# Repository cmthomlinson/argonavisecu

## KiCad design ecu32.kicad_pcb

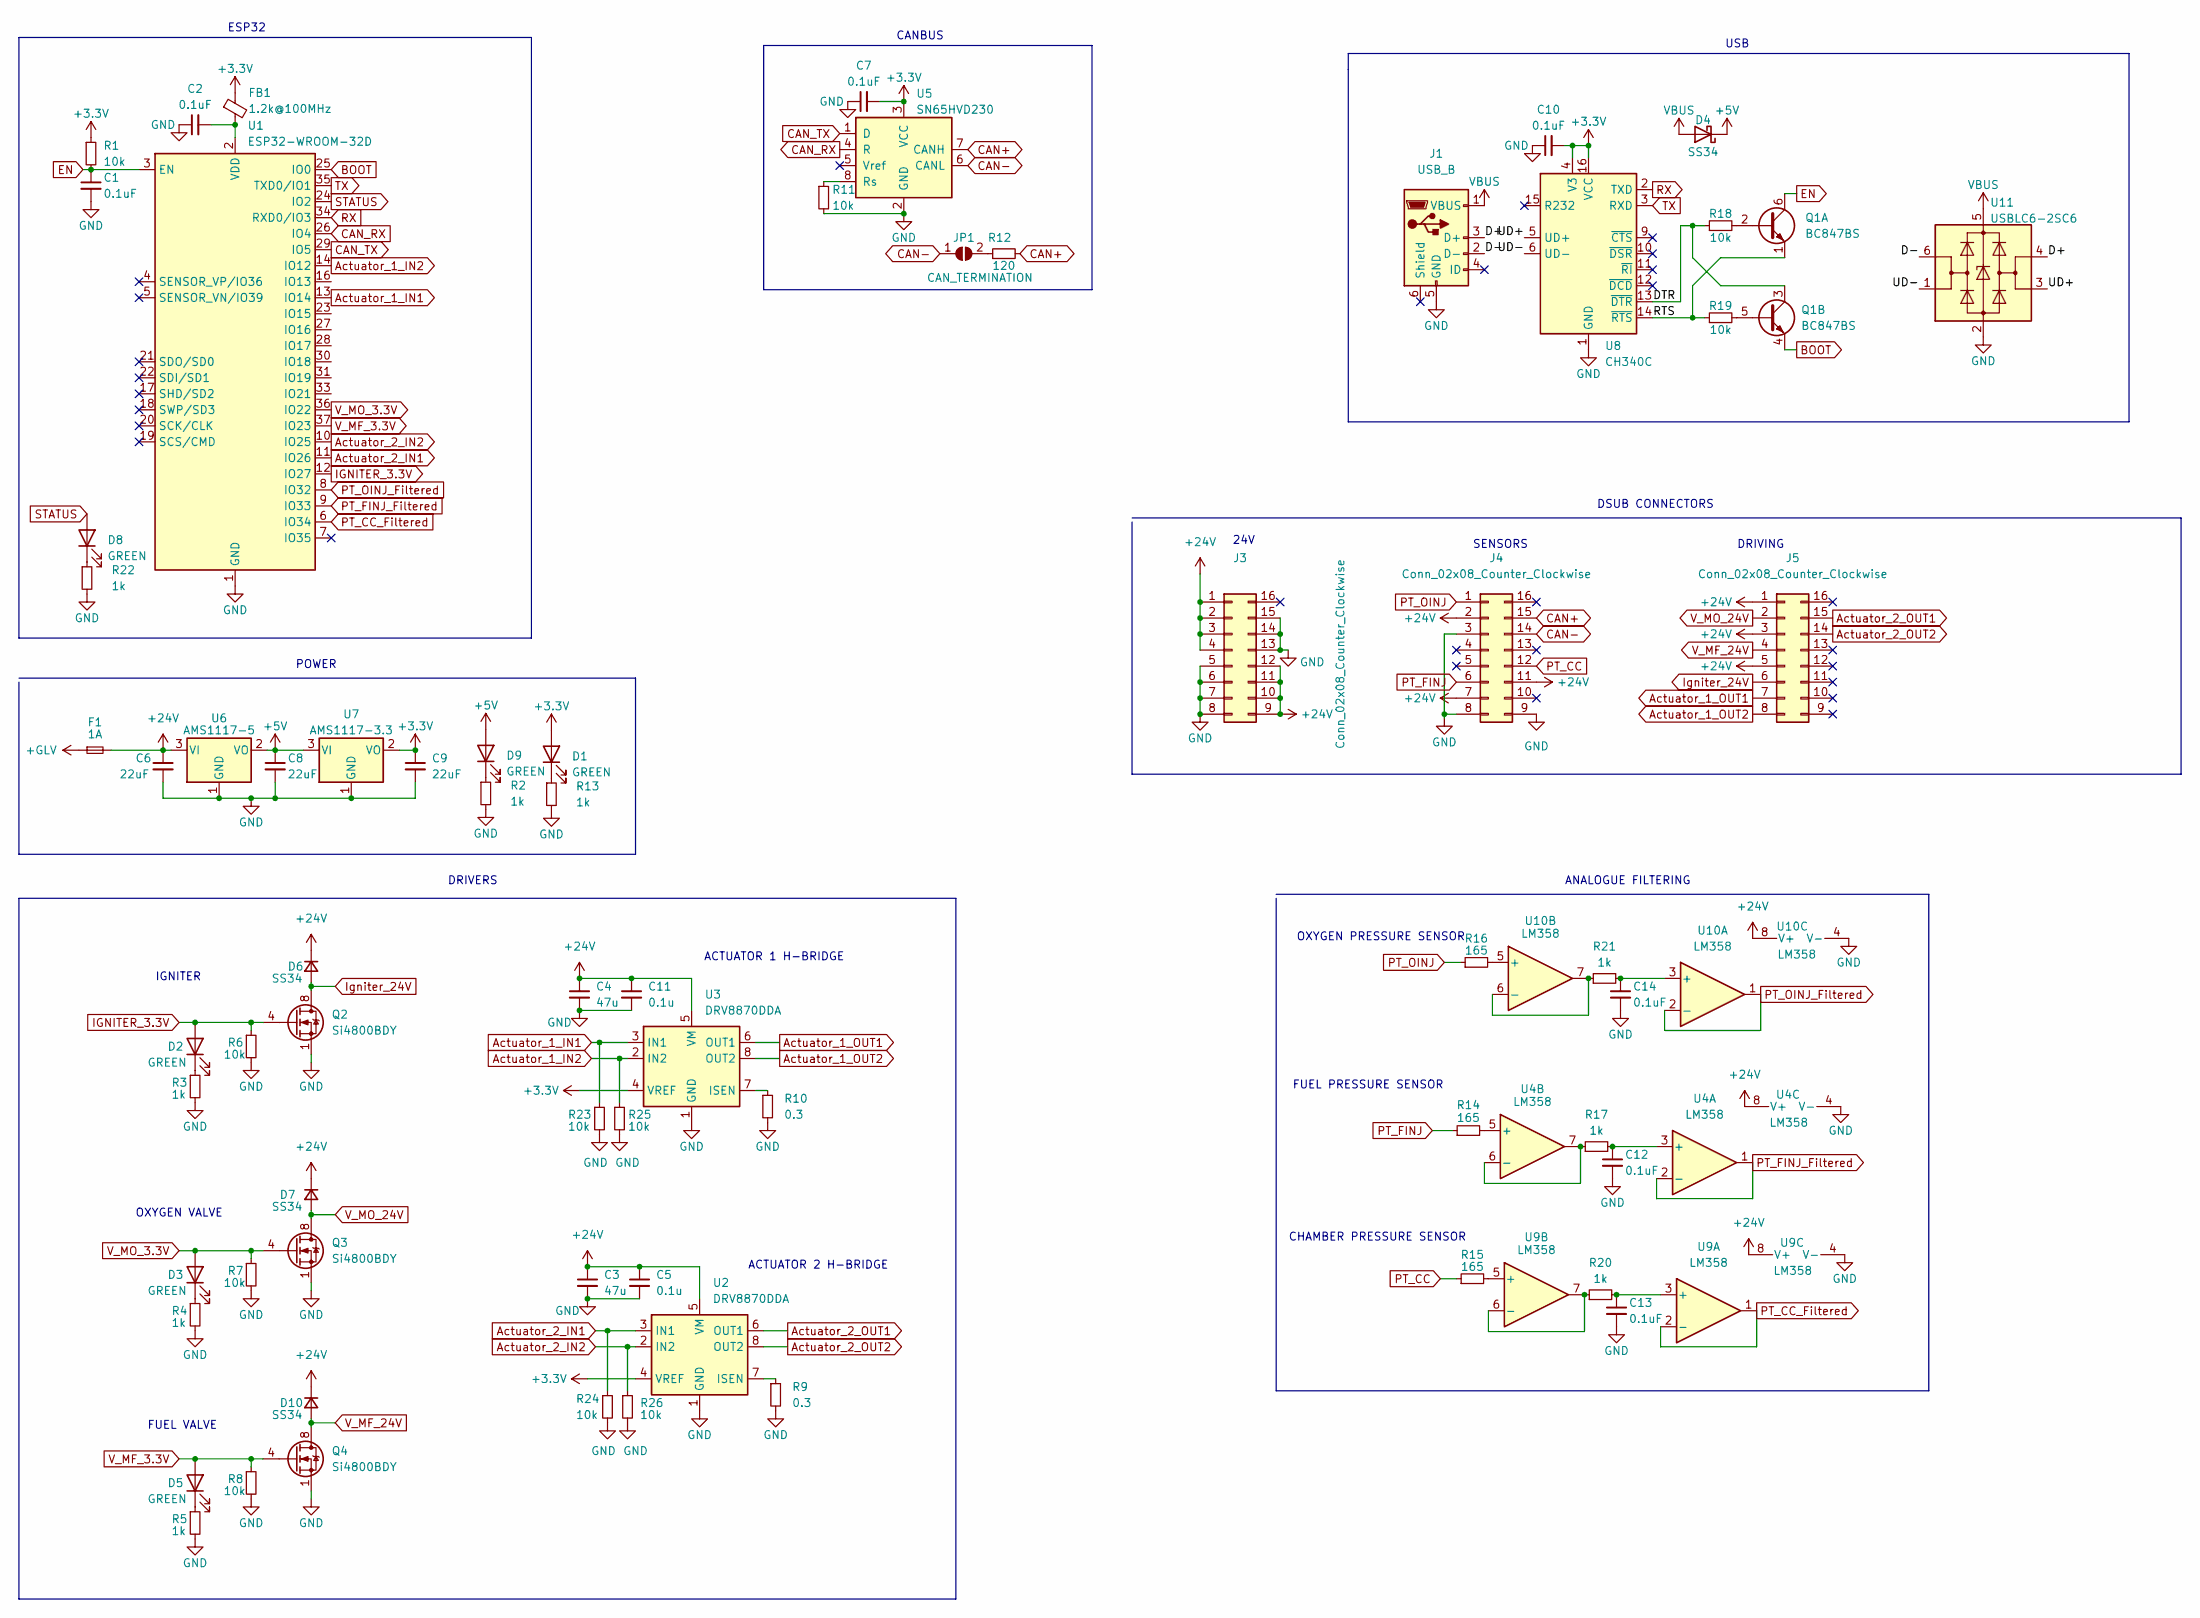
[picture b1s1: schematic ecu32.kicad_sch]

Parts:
C1, C2, C7, C10, C12, C13, C14: 0.1uF; C_0603_1608Metric
C3, C4: 47u; C_1206_3216Metric
C5, C11: 0.1u; C_1206_3216Metric
C6, C8, C9: 22uF; C_1206_3216Metric
D1, D2, D3, D5, D8, D9: GREEN; LED_0603_1608Metric
D4: SS34; D_SMA; LCSC C466502
D6, D7, D10: SS34; D_SMA
F1: 1A; Fuse_1206_3216Metric
FB1: 1.2k@100MHz; L_0603_1608Metric; LCSC C394460
J1: USB_B; USB_Micro-B_Molex-105017-0001
J3, J4, J5: Conn_02x08_Counter_Clockwise; DSUB-15_Male_Horizontal_P2.77x2.84mm_EdgePinOffset9.90mm_Ho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
JP1: CAN_TERMINATION; SolderJumper-2_P1.3mm_Open_RoundedPad1.0x1.5mm
Q1: BC847BS; SOT-363_SC-70-6
Q2, Q3, Q4: Si4800BDY; SOIC-8_3.9x4.9mm_P1.27mm
R1, R6, R7, R8, R11, R18, R19, R23, R24, R25, R26: 10k; R_0603_1608Metric
R2, R3, R4, R5, R13, R17, R20, R21, R22: 1k; R_0603_1608Metric
R9, R10: 0.3; R_1206_3216Metric
R12: 120; R_0603_1608Metric
R14, R15, R16: 165; R_0603_1608Metric
U1: ESP32-WROOM-32D; ESP32-WROOM-32
U2, U3: DRV8870DDA; Texas_HTSOP-8-1EP_3.9x4.9mm_P1.27mm_EP2.95x4.9mm_Mask2.4x3.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
U4, U9, U10: LM358; SOP-8_3.9x4.9mm_P1.27mm
U5: SN65HVD230; SOIC-8_3.9x4.9mm_P1.27mm
U6: AMS1117-5; SOT-223-3_TabPin2
U7: AMS1117-3.3; SOT-223-3_TabPin2
U8: CH340C; SOIC-16_3.9x9.9mm_P1.27mm
U11: USBLC6-2SC6; SOT-23-6

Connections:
+1GLV: F1.1
+3V3: C7.2, C9.1, C10.2, D1.2 (A), FB1.1, R1.1, U2.4 (VREF), U3.4 (VREF), U5.3 (VCC), U7.2 (VO), U8.4 (V3), U8.16 (VCC)
+5V: C8.1, D4.1 (K), D9.2 (A), U6.2 (VO), U7.3 (VI)
/D+: J1.3 (D+), U11.4 (I/O2)
/D-: J1.2 (D-), U11.6 (I/O1)
/DTR: Q1.3 (C2), R18.1, U8.13 (~DTR)
/RTS: Q1.1 (E1), R19.1, U8.14 (~RTS)
/UD+: U8.5 (UD+), U11.3 (I/O2)
/UD-: U8.6 (UD-), U11.1 (I/O1)
Actuator_1_IN1: R23.1, U1.13 (IO14), U3.3 (IN1)
Actuator_1_IN2: R25.1, U1.14 (IO12), U3.2 (IN2)
Actuator_1_OUT1: J5.7, U3.6 (OUT1)
Actuator_1_OUT2: J5.8, U3.8 (OUT2)
Actuator_2_IN1: R24.1, U1.11 (IO26), U2.3 (IN1)
Actuator_2_IN2: R26.1, U1.10 (IO25), U2.2 (IN2)
Actuator_2_OUT1: J5.15, U2.6 (OUT1)
Actuator_2_OUT2: J5.14, U2.8 (OUT2)
BOOT: Q1.4 (E2), U1.25 (IO0)
CAN+: J4.15, R12.2, U5.7 (CANH)
CAN-: J4.14, JP1.1 (A), U5.6 (CANL)
CAN_RX: U1.26 (IO4), U5.4 (R)
CAN_TX: U1.29 (IO5), U5.1 (D)
EN: C1.1, Q1.6 (C1), R1.2, U1.3 (EN)
GND: C1.2, C2.1, C3.2, C4.2, C5.2, C6.2, C7.1, C8.2, C9.2, C10.1, C11.2, C12.2, C13.2, C14.2, J1.5 (GND), J3.5, J3.6, J3.7, J3.8, J3.13, J3.14, J3.15, J4.3, J4.8, J4.9, Q2.1 (S), Q2.2 (S), Q2.3 (S), Q3.1 (S), Q3.2 (S), Q3.3 (S), Q4.1 (S), Q4.2 (S), Q4.3 (S), R2.2, R3.2, R4.2, R5.2, R6.2, R7.2, R8.2, R9.2, R10.2, R11.2, R13.2, R22.2, R23.2, R24.2, R25.2, R26.2, U1.1 (GND), U1.15 (GND), U1.38 (GND), U1.39 (GND), U2.1 (GND), U2.9 (GND), U3.1 (GND), U3.9 (GND), U4.4 (V-), U5.2 (GND), U6.1 (GND), U7.1 (GND), U8.1 (GND), U9.4 (V-), U10.4 (V-), U11.2 (GND)
IGNITER_3.3V: D2.2 (A), Q2.4 (G), R6.1, U1.12 (IO27)
Igniter_24V: D6.2 (A), J5.6, Q2.5 (D), Q2.6 (D), Q2.7 (D), Q2.8 (D)
unnamed: C2.2, FB1.2, U1.2 (VDD)
unnamed: C12.1, R17.2, U4.3 (+)
unnamed: C13.1, R20.2, U9.3 (+)
unnamed: C14.1, R21.2, U10.3 (+)
unnamed: D1.1 (K), R13.1
unnamed: D2.1 (K), R3.1
unnamed: D3.1 (K), R4.1
unnamed: D5.1 (K), R5.1
unnamed: D8.1 (K), R22.1
unnamed: D9.1 (K), R2.1
unnamed: JP1.2 (B), R12.1
unnamed: Q1.2 (B1), R18.2
unnamed: Q1.5 (B2), R19.2
unnamed: R9.1, U2.7 (ISEN)
unnamed: R10.1, U3.7 (ISEN)
unnamed: R11.1, U5.8 (Rs)
unnamed: R14.2, U4.5 (+)
unnamed: R15.2, U9.5 (+)
unnamed: R16.2, U10.5 (+)
unnamed: R17.1, U4.6 (-), U4.7
unnamed: R20.1, U9.6 (-), U9.7
unnamed: R21.1, U10.6 (-), U10.7
PT_CC: J4.12, R15.1
PT_CC_Filtered: U1.6 (IO34), U9.1, U9.2 (-)
PT_FINJ: J4.6, R14.1
PT_FINJ_Filtered: U1.9 (IO33), U4.1, U4.2 (-)
PT_OINJ: J4.1, R16.1
PT_OINJ_Filtered: U1.8 (IO32), U10.1, U10.2 (-)
RX: U1.34 (RXD0/IO3), U8.2 (TXD)
STATUS: D8.2 (A), U1.24 (IO2)
TX: U1.35 (TXD0/IO1), U8.3 (RXD)
VBUS: D4.2 (A), J1.1 (VBUS), U11.5 (VBUS)
V_MF_3.3V: D5.2 (A), Q4.4 (G), R8.1, U1.37 (IO23)
V_MF_24V: D10.2 (A), J5.4, Q4.5 (D), Q4.6 (D), Q4.7 (D), Q4.8 (D)
V_MO_3.3V: D3.2 (A), Q3.4 (G), R7.1, U1.36 (IO22)
V_MO_24V: D7.2 (A), J5.2, Q3.5 (D), Q3.6 (D), Q3.7 (D), Q3.8 (D)

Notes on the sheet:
FUEL VALVE
ACTUATOR 2 H-BRIDGE
OXYGEN VALVE
DRIVERS
DSUB CONNECTORS
CHAMBER PRESSURE SENSOR
CANBUS
ESP32
USB
OXYGEN PRESSURE SENSOR
ANALOGUE FILTERING
24V
POWER
ACTUATOR 1 H-BRIDGE
SENSORS
IGNITER
FUEL PRESSURE SENSOR
DRIVING

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
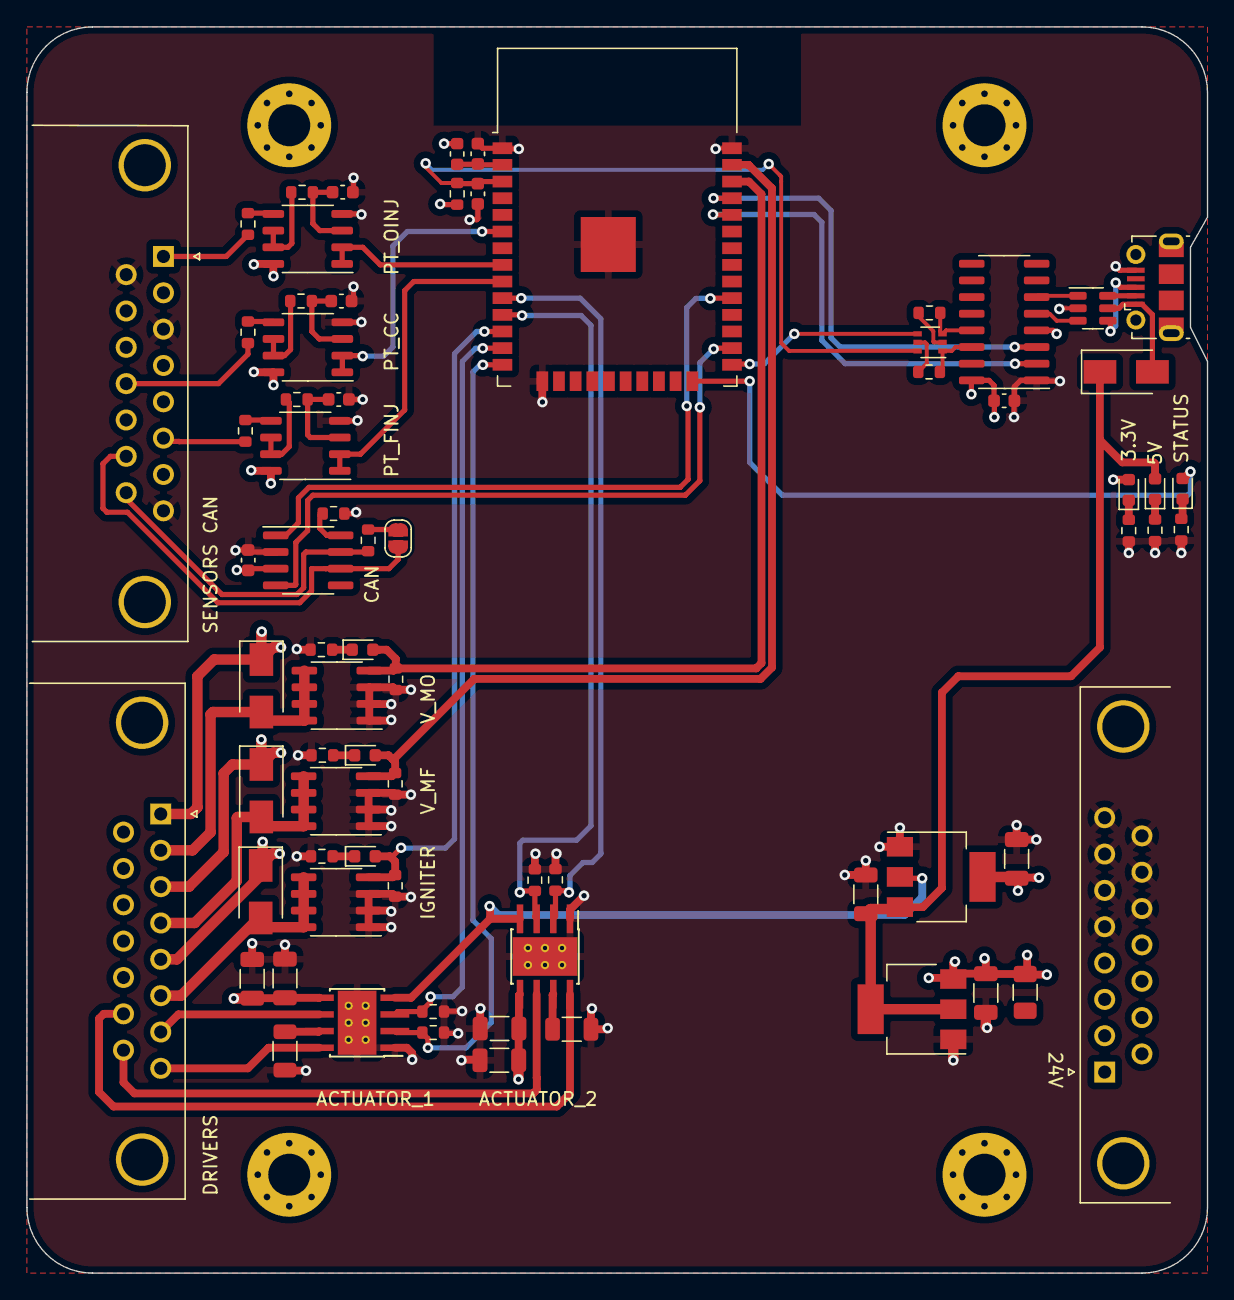
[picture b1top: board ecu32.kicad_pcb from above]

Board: 4 copper layers, 90.0 x 95.0 mm, 72 parts (0 on the bottom side), 62 nets.

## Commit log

2023-01-16 fix error
